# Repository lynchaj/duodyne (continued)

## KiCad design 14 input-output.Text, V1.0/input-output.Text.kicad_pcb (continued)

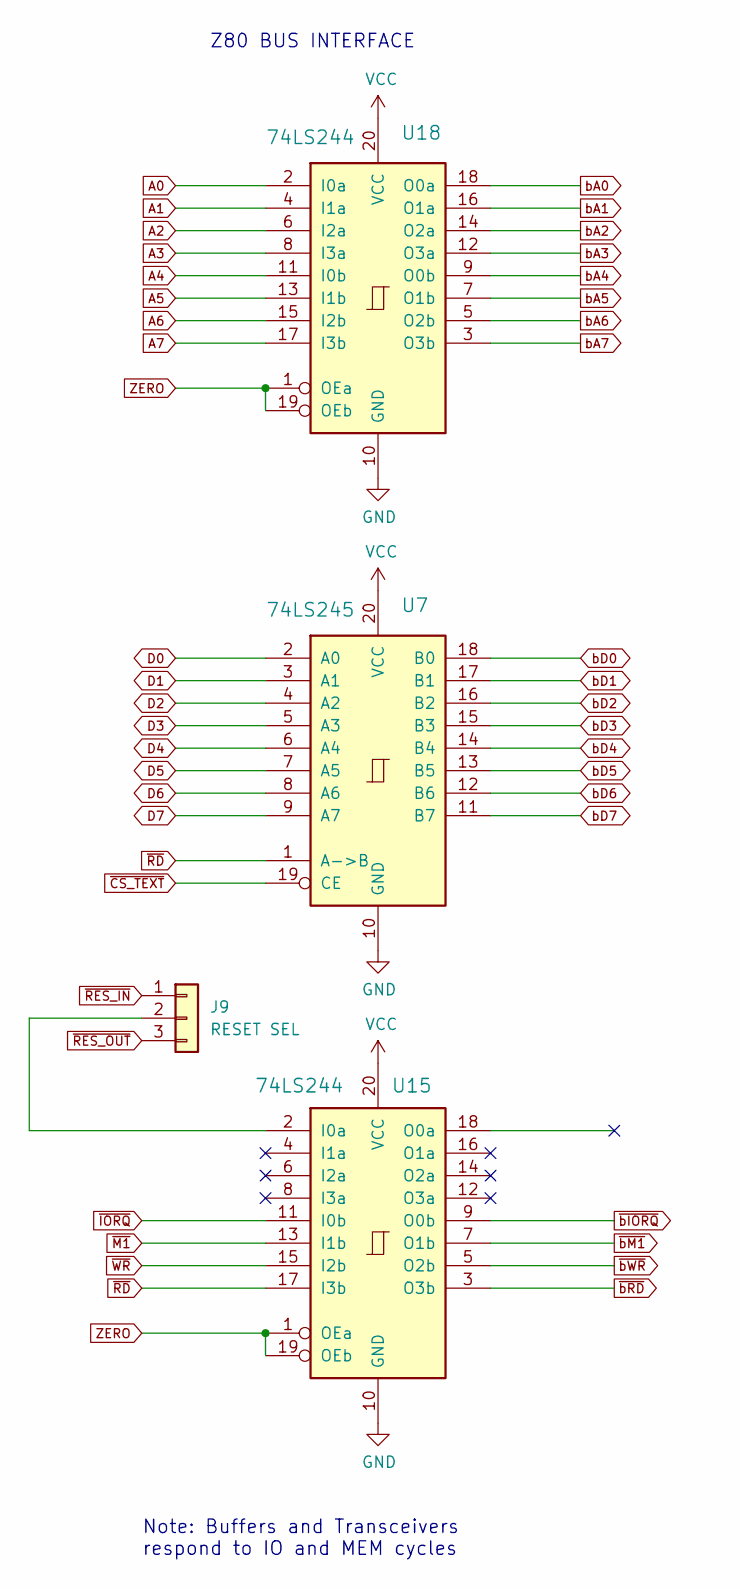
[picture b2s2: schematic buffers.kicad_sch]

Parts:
J9: RESET SEL; PinHeader_1x03_P2.54mm_Vertical
U7: 74LS245; DIP-20_W7.62mm_Socket
U15, U18: 74LS244; DIP-20_W7.62mm_Socket

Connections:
A0: U18.2 (I0a); also elsewhere on the board
A1: U18.4 (I1a); also elsewhere on the board
A2: U18.6 (I2a); also elsewhere on the board
A3: U18.8 (I3a); also elsewhere on the board
A4: U18.11 (I0b); also elsewhere on the board
A5: U18.13 (I1b); also elsewhere on the board
A6: U18.15 (I2b); also elsewhere on the board
A7: U18.17 (I3b); also elsewhere on the board
D0: U7.2 (A0); also elsewhere on the board
D1: U7.3 (A1); also elsewhere on the board
D2: U7.4 (A2); also elsewhere on the board
D3: U7.5 (A3); also elsewhere on the board
D4: U7.6 (A4); also elsewhere on the board
D5: U7.7 (A5); also elsewhere on the board
D6: U7.8 (A6); also elsewhere on the board
D7: U7.9 (A7); also elsewhere on the board
unnamed: J9.2, U15.2 (I0a)
ZERO: U15.1 (OEa), U15.19 (OEb), U18.1 (OEa), U18.19 (OEb); also elsewhere on the board
bA0: U18.18 (O0a); also elsewhere on the board
bA1: U18.16 (O1a); also elsewhere on the board
bA2: U18.14 (O2a); also elsewhere on the board
bA3: U18.12 (O3a); also elsewhere on the board
bA4: U18.9 (O0b); also elsewhere on the board
bA5: U18.7 (O1b); also elsewhere on the board
bA6: U18.5 (O2b); also elsewhere on the board
bA7: U18.3 (O3b); also elsewhere on the board
bD0: U7.18 (B0); also elsewhere on the board
bD1: U7.17 (B1); also elsewhere on the board
bD2: U7.16 (B2); also elsewhere on the board
bD3: U7.15 (B3); also elsewhere on the board
bD4: U7.14 (B4); also elsewhere on the board
bD5: U7.13 (B5); also elsewhere on the board
bD6: U7.12 (B6); also elsewhere on the board
bD7: U7.11 (B7); also elsewhere on the board
~CS_TEXT: U7.19 (CE); also elsewhere on the board
~IORQ: U15.11 (I0b); also elsewhere on the board
~M1: U15.13 (I1b); also elsewhere on the board
~RD: U7.1 (A->B), U15.17 (I3b); also elsewhere on the board
~RES_IN: J9.1; also elsewhere on the board
~RES_OUT: J9.3; also elsewhere on the board
~WR: U15.15 (I2b); also elsewhere on the board
~bIORQ: U15.9 (O0b); also elsewhere on the board
~bM1: U15.7 (O1b); also elsewhere on the board
~bRD: U15.3 (O3b); also elsewhere on the board
~bWR: U15.5 (O2b); also elsewhere on the board

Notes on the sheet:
Z80 BUS INTERFACE
Note: Buffers and Transceivers respond to IO and MEM cycles

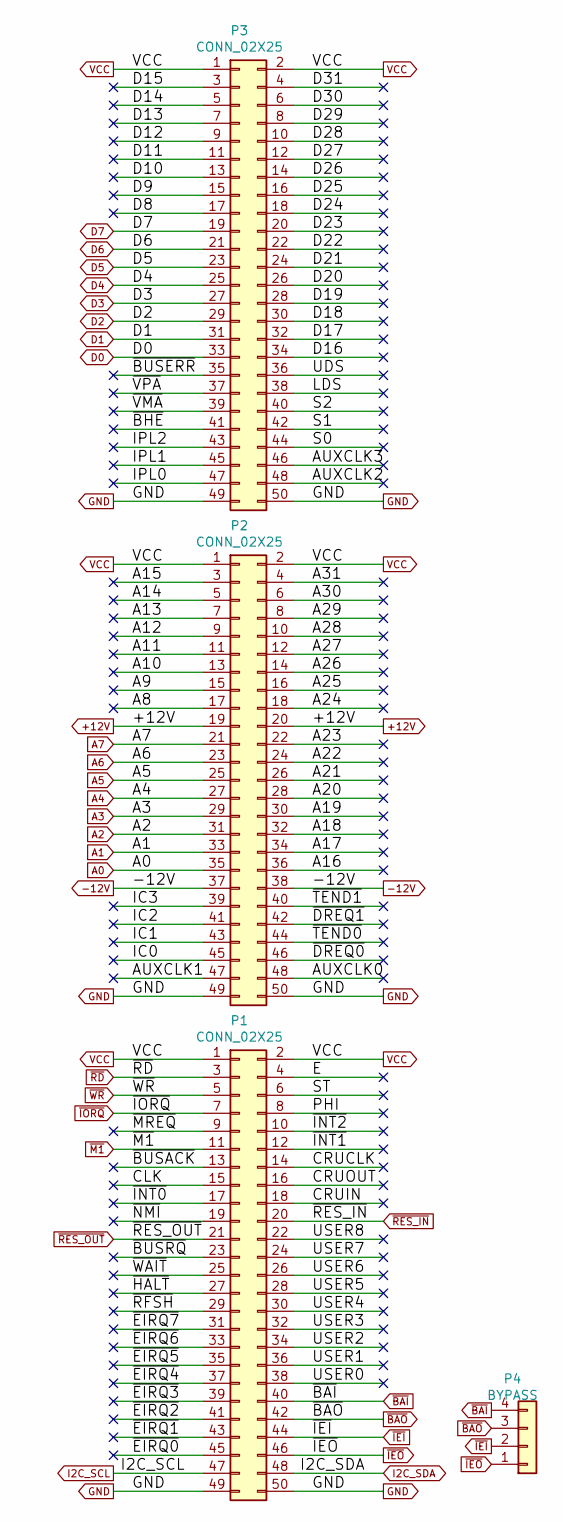
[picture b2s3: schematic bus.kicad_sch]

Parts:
P1, P2, P3: CONN_02X25; IDC-Header_2x25_P2.54mm_Horizontal
P4: BYPASS; PinHeader_1x04_P2.54mm_Vertical

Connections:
+12V: P2.19, P2.20
-12V: P2.37, P2.38
/bus/A8: P2.17
/bus/A9: P2.15
/bus/A10: P2.13
/bus/A11: P2.11
/bus/A12: P2.9
/bus/A13: P2.7
/bus/A14: P2.5
/bus/A15: P2.3
/bus/A16: P2.36
/bus/A17: P2.34
/bus/A18: P2.32
/bus/A19: P2.30
/bus/A20: P2.28
/bus/A21: P2.26
/bus/A22: P2.24
/bus/A23: P2.22
/bus/A24: P2.18
/bus/A25: P2.16
/bus/A26: P2.14
/bus/A27: P2.12
/bus/A28: P2.10
/bus/A29: P2.8
/bus/A30: P2.6
/bus/A31: P2.4
/bus/AUXCLK0: P2.48
/bus/AUXCLK1: P2.47
/bus/AUXCLK2: P3.48
/bus/AUXCLK3: P3.46
/bus/CLK: P1.15
/bus/CRUCLK: P1.14
/bus/CRUIN: P1.18
/bus/CRUOUT: P1.16
/bus/D8: P3.17
/bus/D9: P3.15
/bus/D10: P3.13
/bus/D11: P3.11
/bus/D12: P3.9
/bus/D13: P3.7
/bus/D14: P3.5
/bus/D15: P3.3
/bus/D16: P3.34
/bus/D17: P3.32
/bus/D18: P3.30
/bus/D19: P3.28
/bus/D20: P3.26
/bus/D21: P3.24
/bus/D22: P3.22
/bus/D23: P3.20
/bus/D24: P3.18
/bus/D25: P3.16
/bus/D26: P3.14
/bus/D27: P3.12
/bus/D28: P3.10
/bus/D29: P3.8
/bus/D30: P3.6
/bus/D31: P3.4
/bus/E: P1.4
/bus/I2C_SCL: P1.47
/bus/I2C_SDA: P1.48
/bus/IC0: P2.45
/bus/IC1: P2.43
/bus/IC2: P2.41
/bus/IC3: P2.39
/bus/IPL0: P3.47
/bus/IPL1: P3.45
/bus/IPL2: P3.43
/bus/LDS: P3.38
/bus/PHI: P1.8
/bus/S0: P3.44
/bus/S1: P3.42
/bus/S2: P3.40
/bus/ST: P1.6
/bus/UDS: P3.36
/bus/USER0: P1.38
/bus/USER1: P1.36
/bus/USER2: P1.34
/bus/USER3: P1.32
/bus/USER4: P1.30
/bus/USER5: P1.28
/bus/USER6: P1.26
/bus/USER7: P1.24
/bus/USER8: P1.22
/bus/~BHE: P3.41
/bus/~BUSACK: P1.13
/bus/~BUSERR: P3.35
/bus/~BUSRQ: P1.23
/bus/~DREQ0: P2.46
/bus/~DREQ1: P2.42
/bus/~EIRQ0: P1.45
/bus/~EIRQ1: P1.43
/bus/~EIRQ2: P1.41
/bus/~EIRQ3: P1.39
/bus/~EIRQ4: P1.37
/bus/~EIRQ5: P1.35
/bus/~EIRQ6: P1.33
/bus/~EIRQ7: P1.31
/bus/~HALT: P1.27
/bus/~INT0: P1.17
/bus/~INT1: P1.12
/bus/~INT2: P1.10
/bus/~MREQ: P1.9
/bus/~NMI: P1.19
/bus/~RFSH: P1.29
/bus/~TEND0: P2.44
/bus/~TEND1: P2.40
/bus/~VMA: P3.39
/bus/~VPA: P3.37
/bus/~WAIT: P1.25
A0: P2.35; also elsewhere on the board
A1: P2.33; also elsewhere on the board
A2: P2.31; also elsewhere on the board
A3: P2.29; also elsewhere on the board
A4: P2.27; also elsewhere on the board
A5: P2.25; also elsewhere on the board
A6: P2.23; also elsewhere on the board
A7: P2.21; also elsewhere on the board
D0: P3.33; also elsewhere on the board
D1: P3.31; also elsewhere on the board
D2: P3.29; also elsewhere on the board
D3: P3.27; also elsewhere on the board
D4: P3.25; also elsewhere on the board
D5: P3.23; also elsewhere on the board
D6: P3.21; also elsewhere on the board
D7: P3.19; also elsewhere on the board
~BAI: P1.40, P4.4
~BAO: P1.42, P4.3
~IEI: P1.44, P4.2
~IEO: P1.46, P4.1
~IORQ: P1.7; also elsewhere on the board
~M1: P1.11; also elsewhere on the board
~RD: P1.3; also elsewhere on the board
~RES_IN: P1.20; also elsewhere on the board
~RES_OUT: P1.21; also elsewhere on the board
~WR: P1.5; also elsewhere on the board

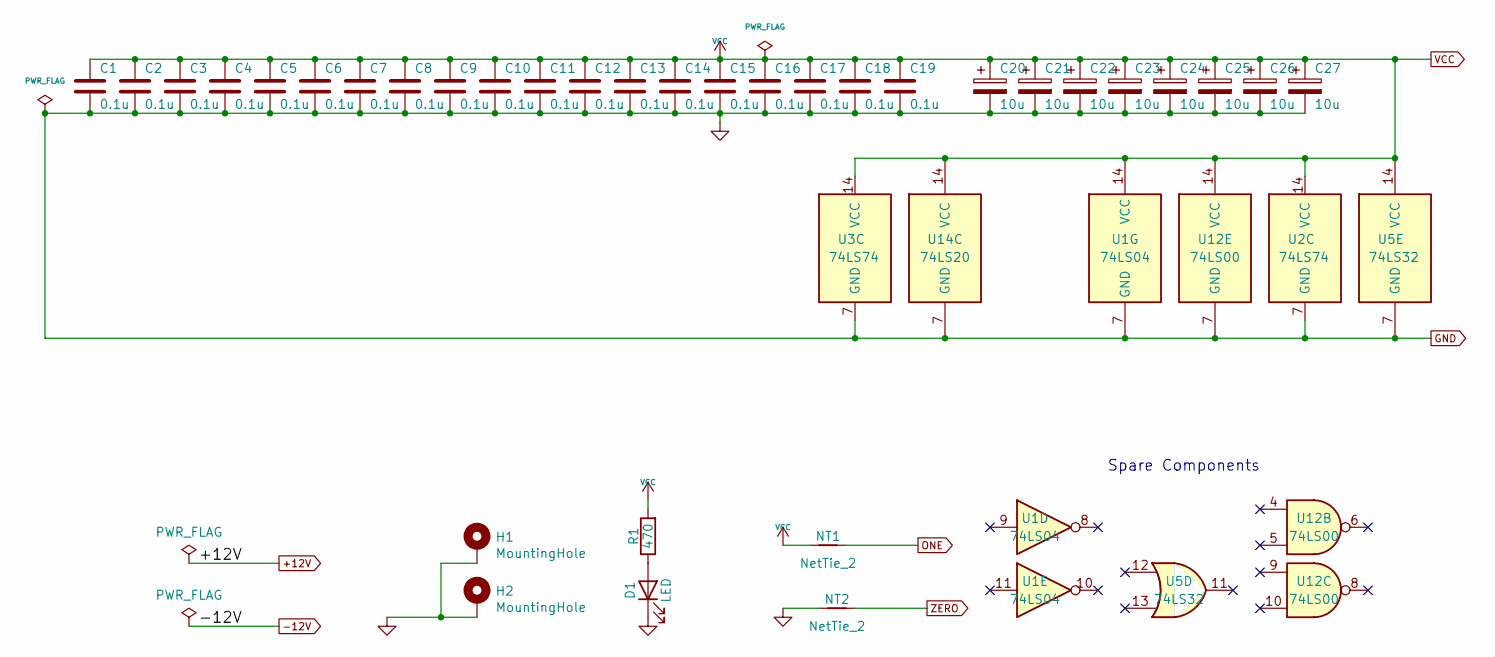
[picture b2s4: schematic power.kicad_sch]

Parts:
C1, C2, C3, C4, C5, C6, C7, C8, C9, C10, C11, C12, C13, C14, C15, C16, C17, C18, C19: 0.1u; C_Disc_D5.0mm_W2.5mm_P5.00mm
C20, C21, C22, C23, C24, C25, C26, C27: 10u; CP_Radial_D5.0mm_P2.50mm
D1: LED; LED_D3.0mm_Horizontal_O3.81mm_Z2.0mm
H1, H2: MountingHole; MountingHole_3.2mm_M3_Pad
NT1, NT2: NetTie_2; NetTie-2_THT_Pad0.3mm
R1: 470; R_Axial_DIN0207_L6.3mm_D2.5mm_P7.62mm_Horizontal
U1: 74LS04; DIP-14_W7.62mm
U2, U3: 74LS74; DIP-14_W7.62mm
U5: 74LS32; DIP-14_W7.62mm
U12: 74LS00; DIP-14_W7.62mm
U14: 74LS20; DIP-14_W7.62mm

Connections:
unnamed: D1.2 (A), R1.1
ZERO: NT2.2; also elsewhere on the board

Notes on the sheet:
Spare Components

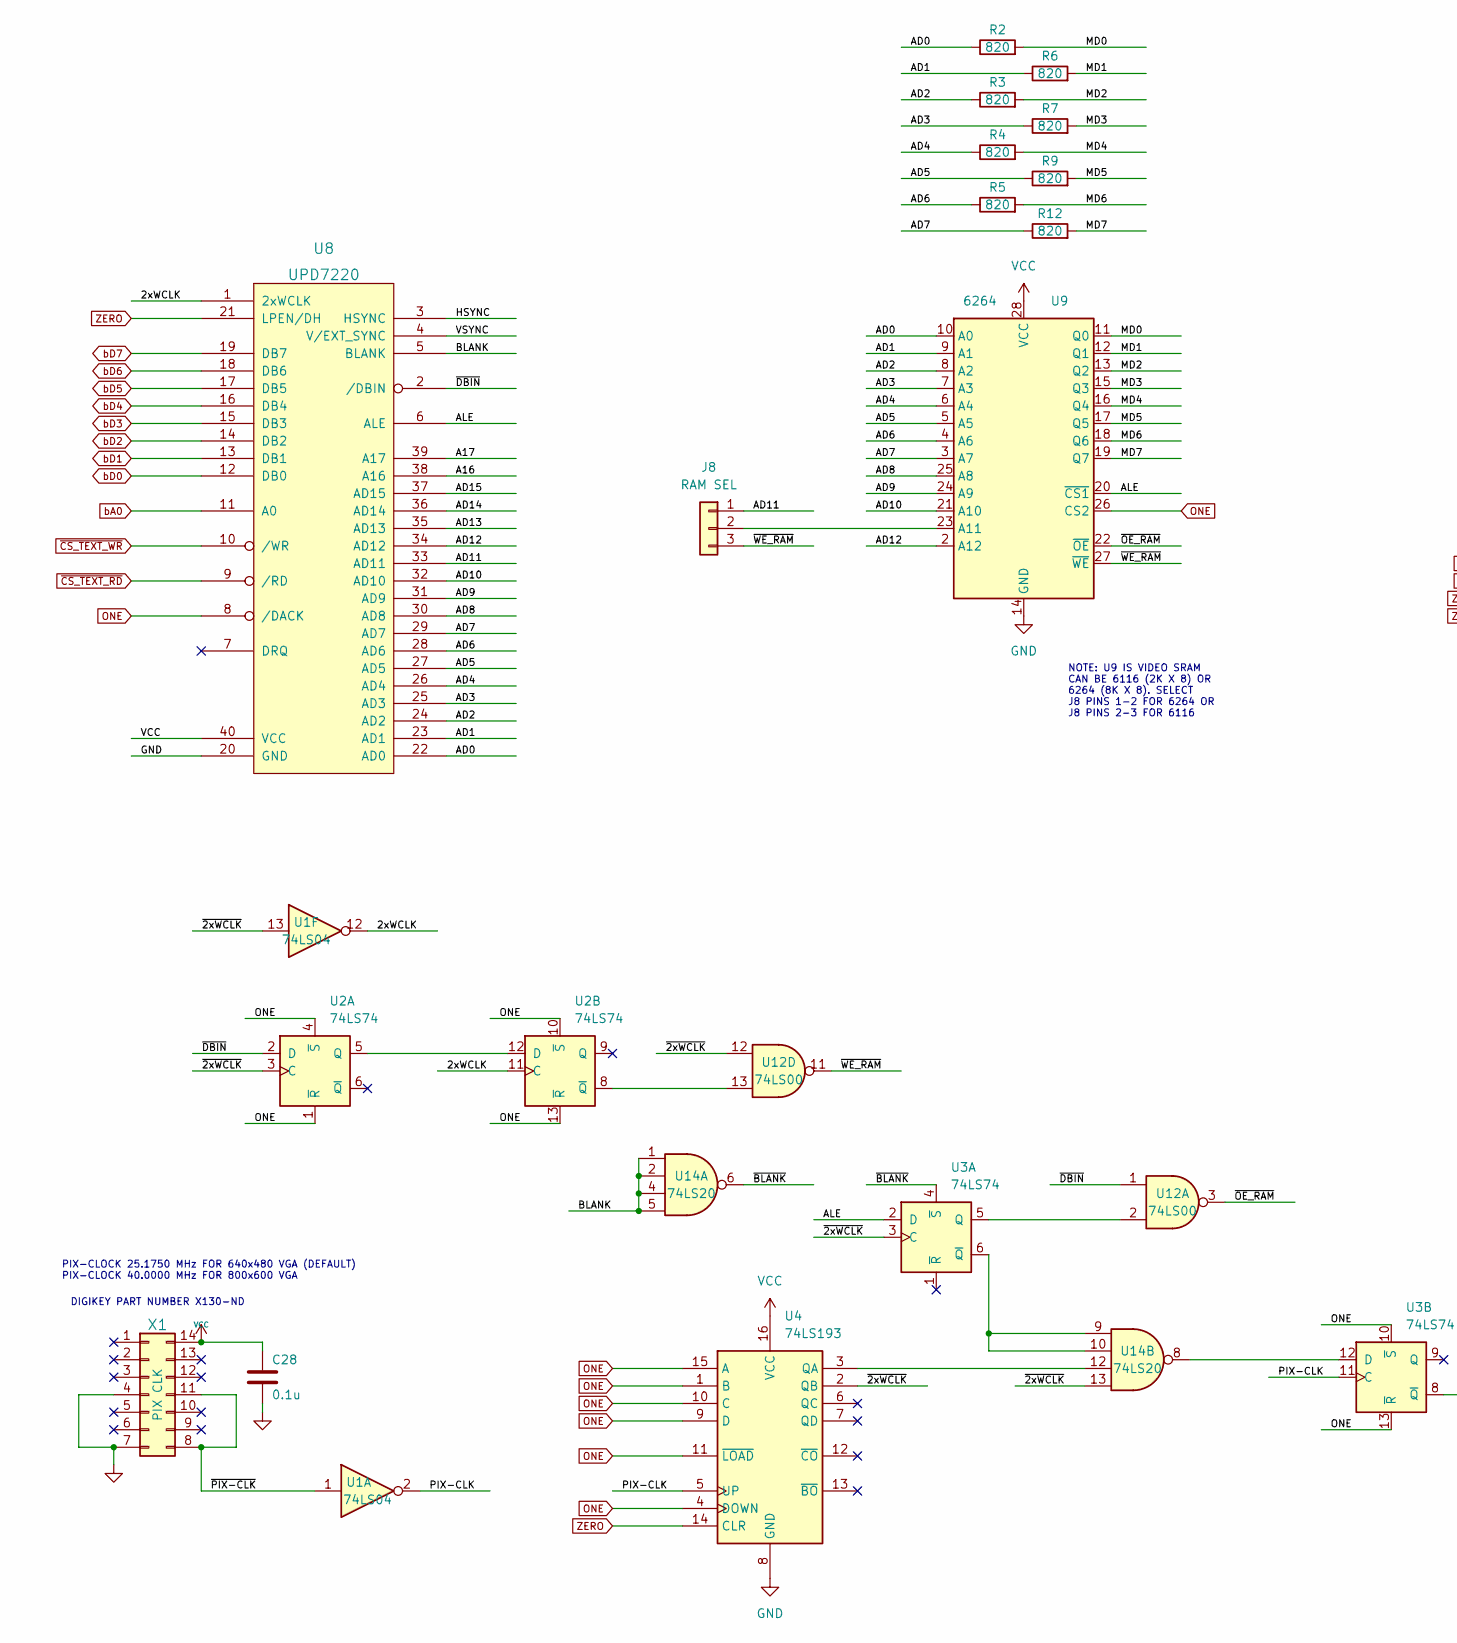
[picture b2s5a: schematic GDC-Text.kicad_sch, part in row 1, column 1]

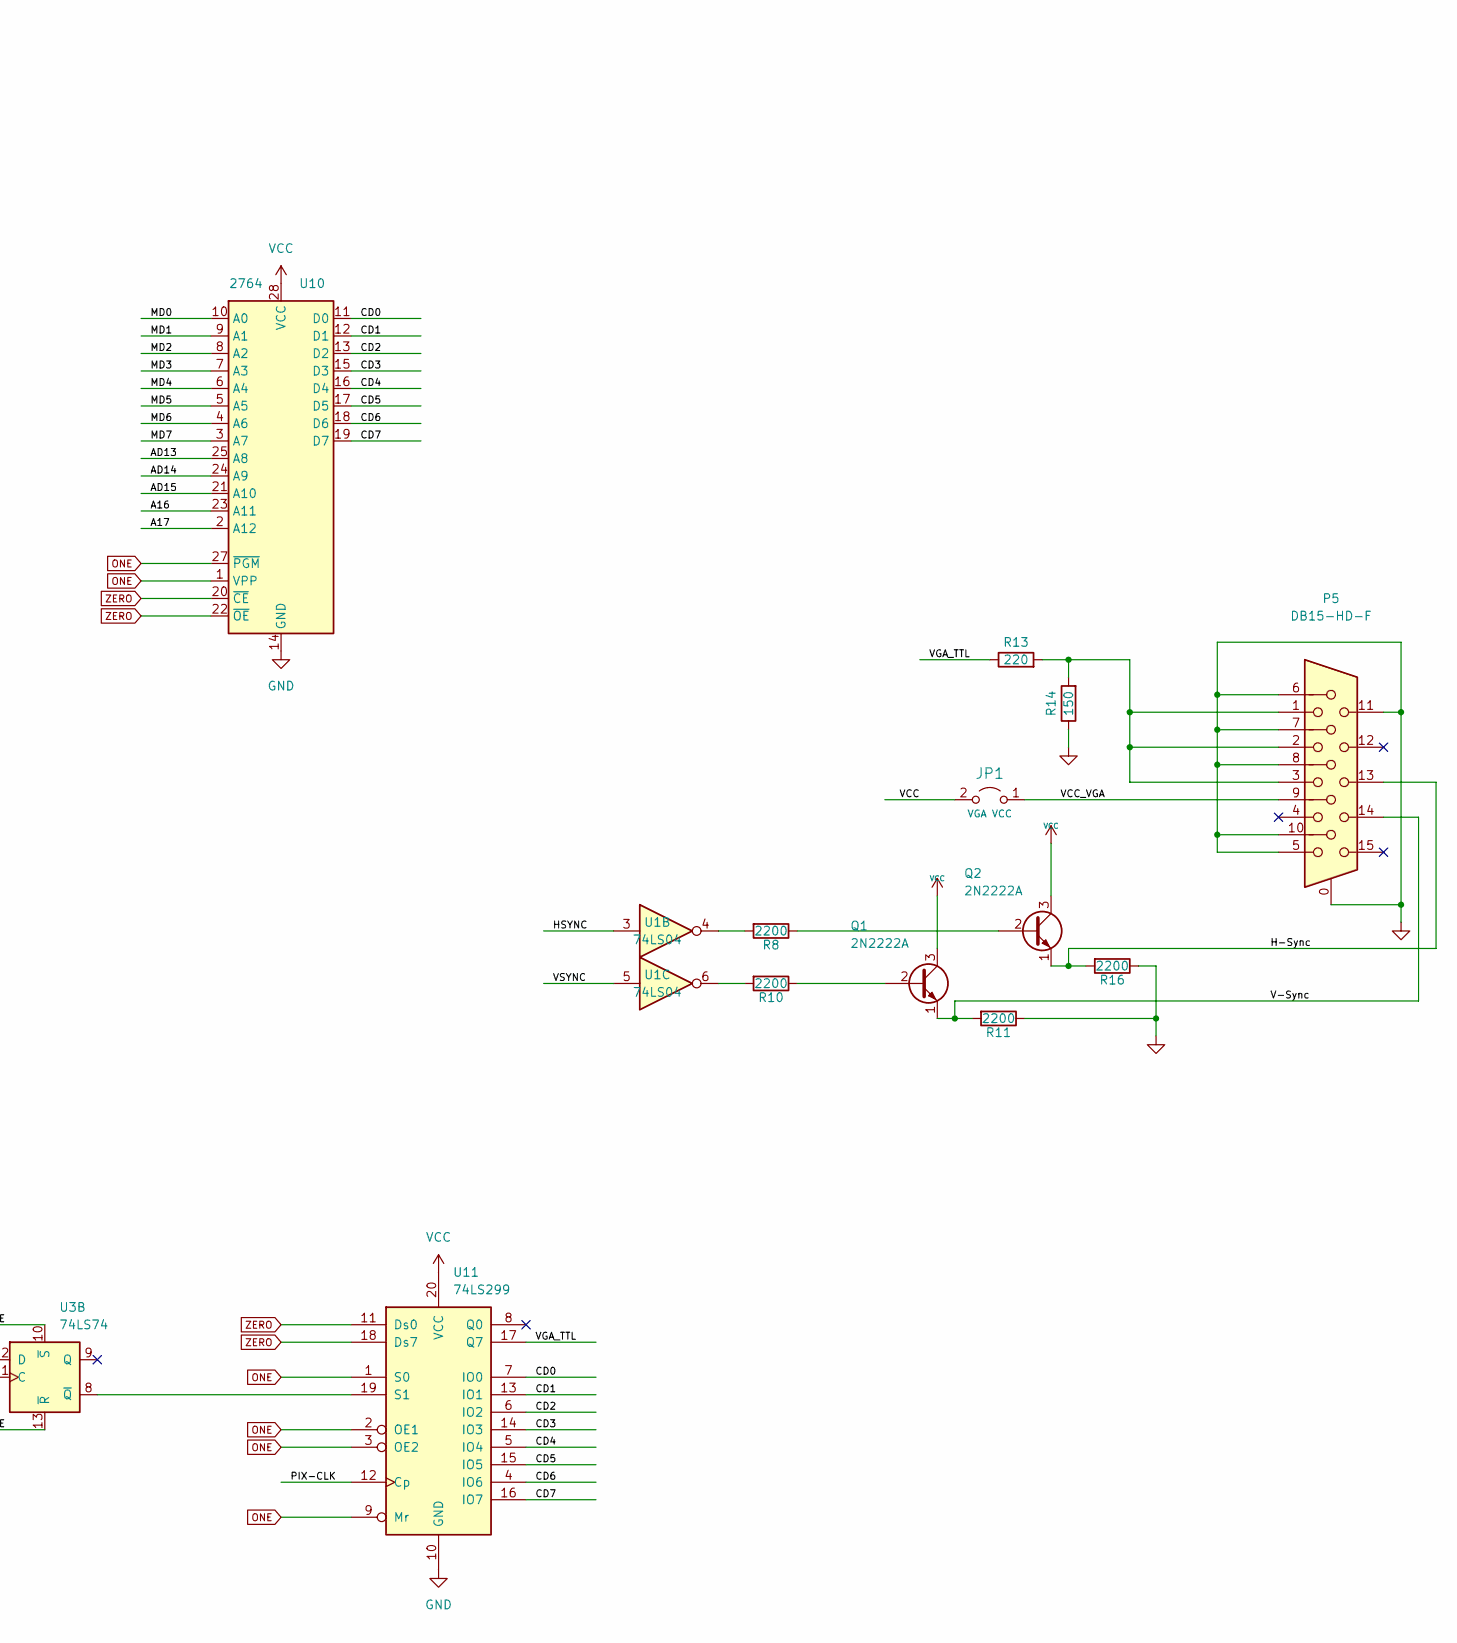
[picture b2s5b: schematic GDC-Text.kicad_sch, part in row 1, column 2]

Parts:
C28: 0.1u; C_Disc_D5.0mm_W2.5mm_P5.00mm
J8: RAM SEL; PinHeader_1x03_P2.54mm_Vertical
JP1: VGA VCC; PinHeader_1x02_P2.54mm_Vertical
P5: DB15-HD-F; DSUB-15-HD_Female_Horizontal_P2.29x1.98mm_EdgePinOffset3.03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
Q1, Q2: 2N2222A; TO-92L_Inline
R2, R3, R4, R5, R6, R7, R9, R12: 820; R_Axial_DIN0207_L6.3mm_D2.5mm_P7.62mm_Horizontal
R8, R10, R11, R16: 2200; R_Axial_DIN0207_L6.3mm_D2.5mm_P7.62mm_Horizontal
R13: 220; R_Axial_DIN0207_L6.3mm_D2.5mm_P7.62mm_Horizontal
R14: 150; R_Axial_DIN0207_L6.3mm_D2.5mm_P7.62mm_Horizontal
U1: 74LS04; DIP-14_W7.62mm
U2, U3: 74LS74; DIP-14_W7.62mm
U4: 74LS193; DIP-16_W7.62mm
U8: UPD7220; DIP-40_W15.24mm
U9: 6264; DIP-28_W15.24mm
U10: 2764; DIP-28_W15.24mm
U11: 74LS299; DIP-20_W7.62mm
U12: 74LS00; DIP-14_W7.62mm
U14: 74LS20; DIP-14_W7.62mm
X1: PIX CLK; DIP-14_W7.62mm

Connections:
/GDC-Text/2xWCLK: U1.12, U2.11 (C), U8.1 (2xWCLK)
/GDC-Text/A16: U8.38 (A16), U10.23 (A11)
/GDC-Text/A17: U8.39 (A17), U10.2 (A12)
/GDC-Text/AD0: R2.1, U8.22 (AD0), U9.10 (A0)
/GDC-Text/AD1: R6.1, U8.23 (AD1), U9.9 (A1)
/GDC-Text/AD2: R3.1, U8.24 (AD2), U9.8 (A2)
/GDC-Text/AD3: R7.1, U8.25 (AD3), U9.7 (A3)
/GDC-Text/AD4: R4.1, U8.26 (AD4), U9.6 (A4)
/GDC-Text/AD5: R9.1, U8.27 (AD5), U9.5 (A5)
/GDC-Text/AD6: R5.1, U8.28 (AD6), U9.4 (A6)
/GDC-Text/AD7: R12.1, U8.29 (AD7), U9.3 (A7)
/GDC-Text/AD8: U8.30 (AD8), U9.25 (A8)
/GDC-Text/AD9: U8.31 (AD9), U9.24 (A9)
/GDC-Text/AD10: U8.32 (AD10), U9.21 (A10)
/GDC-Text/AD11: J8.1, U8.33 (AD11)
/GDC-Text/AD12: U8.34 (AD12), U9.2 (A12)
/GDC-Text/AD13: U8.35 (AD13), U10.25 (A8)
/GDC-Text/AD14: U8.36 (AD14), U10.24 (A9)
/GDC-Text/AD15: U8.37 (AD15), U10.21 (A10)
/GDC-Text/ALE: U3.2 (D), U8.6 (ALE), U9.20 (~CS1)
/GDC-Text/BLANK: U8.5 (BLANK), U14.1, U14.2, U14.4, U14.5
/GDC-Text/CD0: U10.11 (D0), U11.7 (IO0)
/GDC-Text/CD1: U10.12 (D1), U11.13 (IO1)
/GDC-Text/CD2: U10.13 (D2), U11.6 (IO2)
/GDC-Text/CD3: U10.15 (D3), U11.14 (IO3)
/GDC-Text/CD4: U10.16 (D4), U11.5 (IO4)
/GDC-Text/CD5: U10.17 (D5), U11.15 (IO5)
/GDC-Text/CD6: U10.18 (D6), U11.4 (IO6)
/GDC-Text/CD7: U10.19 (D7), U11.16 (IO7)
/GDC-Text/H-Sync: P5.13, Q2.1 (E), R16.2
/GDC-Text/HSYNC: U1.3, U8.3 (HSYNC)
/GDC-Text/MD0: R2.2, U9.11 (Q0), U10.10 (A0)
/GDC-Text/MD1: R6.2, U9.12 (Q1), U10.9 (A1)
/GDC-Text/MD2: R3.2, U9.13 (Q2), U10.8 (A2)
/GDC-Text/MD3: R7.2, U9.15 (Q3), U10.7 (A3)
/GDC-Text/MD4: R4.2, U9.16 (Q4), U10.6 (A4)
/GDC-Text/MD5: R9.2, U9.17 (Q5), U10.5 (A5)
/GDC-Text/MD6: R5.2, U9.18 (Q6), U10.4 (A6)
/GDC-Text/MD7: R12.2, U9.19 (Q7), U10.3 (A7)
/GDC-Text/PIX-CLK: U1.2, U3.11 (C), U4.5 (UP), U11.12 (Cp)
/GDC-Text/V-Sync: P5.14, Q1.1 (E), R11.2
/GDC-Text/VCC_VGA: JP1.1 (A), P5.9
/GDC-Text/VGA_TTL: R13.1, U11.17 (Q7)
/GDC-Text/VSYNC: U1.5, U8.4 (V/EXT_SYNC)
/GDC-Text/~2xWCLK: U1.13, U2.3 (C), U3.3 (C), U4.2 (QB), U12.12, U14.13
/GDC-Text/~BLANK: U3.4 (~S), U14.6
/GDC-Text/~DBIN: U2.2 (D), U8.2 (/DBIN), U12.1
/GDC-Text/~OE_RAM: U9.22 (~OE), U12.3
/GDC-Text/~PIX-CLK: U1.1, X1.8, X1.11
/GDC-Text/~WE_RAM: J8.3, U9.27 (~WE), U12.11
unnamed: J8.2, U9.23 (A11)
unnamed: P5.1, P5.2, P5.3, R13.2, R14.2
unnamed: Q1.2 (B), R10.1
unnamed: Q2.2 (B), R8.1
unnamed: R8.2, U1.4
unnamed: R10.2, U1.6
unnamed: U2.5 (Q), U2.12 (D)
unnamed: U3.8 (~Q), U11.19 (S1)
unnamed: U3.5 (Q), U12.2
unnamed: U2.8 (~Q), U12.13
unnamed: U3.12 (D), U14.8
unnamed: U3.6 (~Q), U14.9, U14.10
unnamed: U4.3 (QA), U14.12
ZERO: U4.14 (CLR), U8.21 (LPEN/DH), U10.20 (~CE), U10.22 (~OE), U11.11 (Ds0), U11.18 (Ds7); also elsewhere on the board
bA0: U8.11 (A0); also elsewhere on the board
bD0: U8.12 (DB0); also elsewhere on the board
bD1: U8.13 (DB1); also elsewhere on the board
bD2: U8.14 (DB2); also elsewhere on the board
bD3: U8.15 (DB3); also elsewhere on the board
bD4: U8.16 (DB4); also elsewhere on the board
bD5: U8.17 (DB5); also elsewhere on the board
bD6: U8.18 (DB6); also elsewhere on the board
bD7: U8.19 (DB7); also elsewhere on the board
~CS_TEXT_RD: U8.9 (/RD); also elsewhere on the board
~CS_TEXT_WR: U8.10 (/WR); also elsewhere on the board

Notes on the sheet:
DIGIKEY PART NUMBER X130-ND
PIX-CLOCK 25.1750 MHz FOR 640x480 VGA (DEFAULT) PIX-CLOCK 40.0000 MHz FOR 800x600 VGA
NOTE: U9 IS VIDEO SRAM CAN BE 6116 (2K X 8) OR 6264 (8K X 8). SELECT J8 PINS 1-2 FOR 6264 OR J8 PINS 2-3 FOR 6116

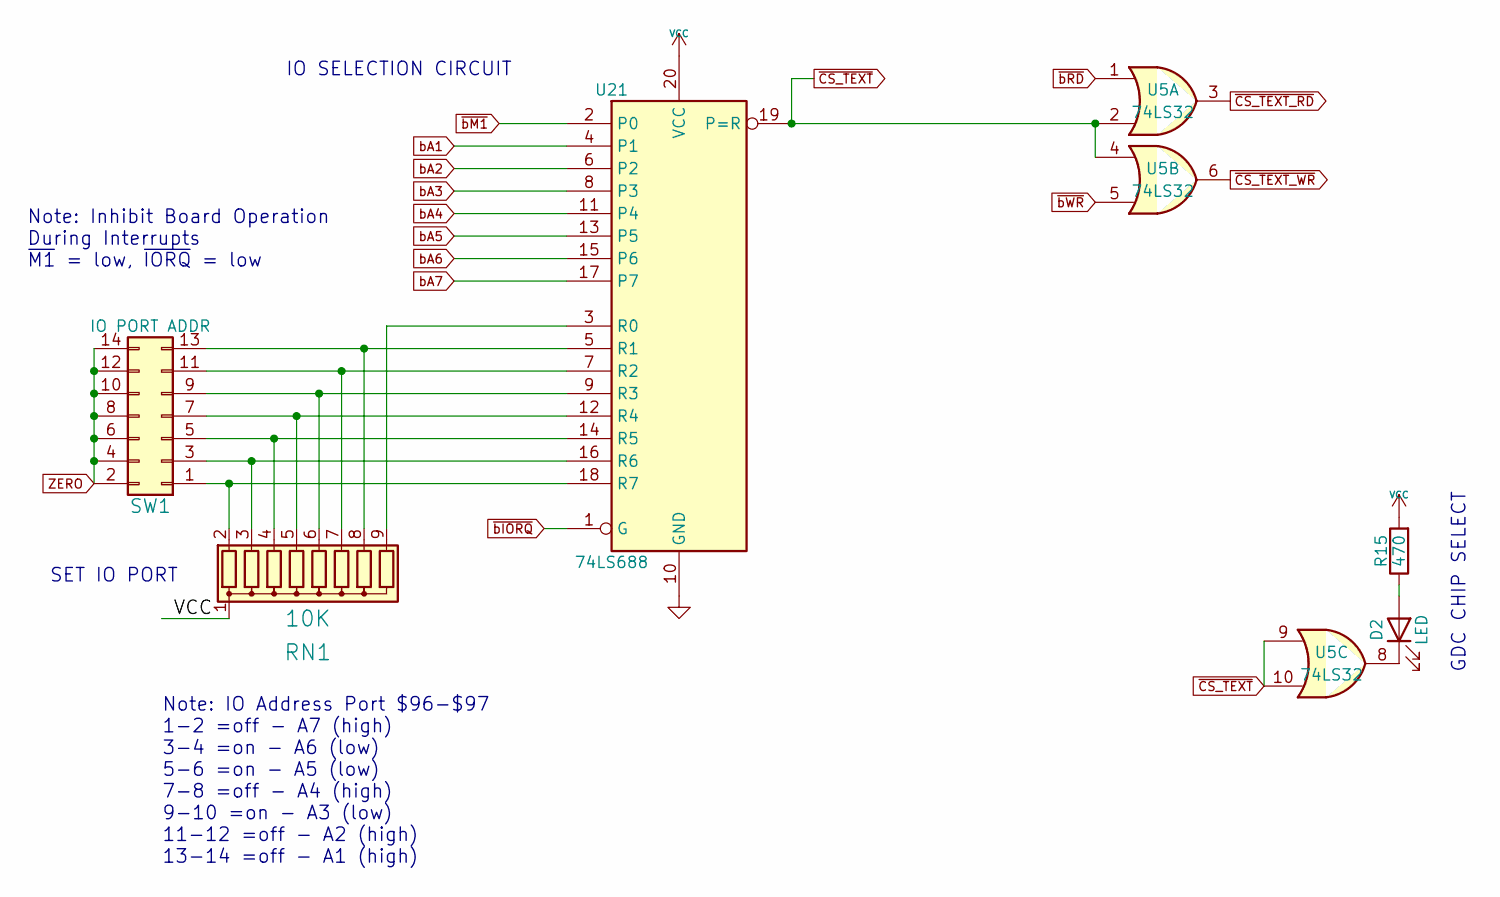
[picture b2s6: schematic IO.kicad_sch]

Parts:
D2: LED; LED_D3.0mm_Horizontal_O3.81mm_Z2.0mm
R15: 470; R_Axial_DIN0207_L6.3mm_D2.5mm_P7.62mm_Horizontal
RN1: 10K; R_Array_SIP9
SW1: IO PORT ADDR; PinHeader_2x07_P2.54mm_Vertical
U5: 74LS32; DIP-14_W7.62mm
U21: 74LS688; DIP-20_W7.62mm

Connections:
unnamed: D2.1 (K), U5.8
unnamed: D2.2 (A), R15.1
unnamed: RN1.2 (R1), SW1.1, U21.18 (R7)
unnamed: RN1.3 (R2), SW1.3, U21.16 (R6)
unnamed: RN1.4 (R3), SW1.5, U21.14 (R5)
unnamed: RN1.5 (R4), SW1.7, U21.12 (R4)
unnamed: RN1.6 (R5), SW1.9, U21.9 (R3)
unnamed: RN1.7 (R6), SW1.11, U21.7 (R2)
unnamed: RN1.8 (R7), SW1.13, U21.5 (R1)
unnamed: RN1.9 (R8), U21.3 (R0)
ZERO: SW1.2, SW1.4, SW1.6, SW1.8, SW1.10, SW1.12, SW1.14; also elsewhere on the board
bA1: U21.4 (P1); also elsewhere on the board
bA2: U21.6 (P2); also elsewhere on the board
bA3: U21.8 (P3); also elsewhere on the board
bA4: U21.11 (P4); also elsewhere on the board
bA5: U21.13 (P5); also elsewhere on the board
bA6: U21.15 (P6); also elsewhere on the board
bA7: U21.17 (P7); also elsewhere on the board
~CS_TEXT_RD: U5.3; also elsewhere on the board
~CS_TEXT_WR: U5.6; also elsewhere on the board
~CS_TEXT: U5.2, U5.4, U5.9, U5.10, U21.19 (P=R); also elsewhere on the board
~bIORQ: U21.1 (G); also elsewhere on the board
~bM1: U21.2 (P0); also elsewhere on the board
~bRD: U5.1; also elsewhere on the board
~bWR: U5.5; also elsewhere on the board

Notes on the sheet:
SET IO PORT
Note: IO Address Port $96-$97 1-2 =off - A7 (high) 3-4 =on - A6 (low) 5-6 =on - A5 (low) 7-8 =off - A4 (high) 9-10 =on - A3 (low) 11-12 =off - A2 (high) 13-14 =off - A1 (high)
IO SELECTION CIRCUIT
Note: Inhibit Board Operation During Interrupts ~{M1} = low, ~{IORQ} = low
GDC CHIP SELECT

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
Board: 2 copper layers, 87 parts (0 on the bottom side), 130 nets, no tracks yet.
